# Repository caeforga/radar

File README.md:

# 📡 Software Radar

Sistema de control y visualización para radar meteorológico con interfaz gráfica moderna desarrollada en Python.

## 📋 Descripción

Software Radar es una aplicación de escritorio diseñada para controlar y visualizar datos de un sistema de radar meteorológico en tiempo real. Incluye control de motores, adquisición de datos GPS, integración con sensores meteorológicos y visualización polar de los datos capturados.

### ✨ Características Principales

- 🎮 **Control de Motores**: Control preciso de rotación e inclinación del radar
- 📊 **Visualización en Tiempo Real**: Gráficos polares actualizados en tiempo real
- 🌍 **Integración GPS**: Captura de coordenadas y orientación
- 🌤️ **Datos Meteorológicos**: Monitoreo de temperatura, viento y precipitaciones
- 🔧 **Configuración Avanzada**: Ajuste de ganancia, rango y modos de operación
- 🤖 **Simulación 3D**: Visualización del modelo cinemático del robot
- 💾 **Registro de Datos**: Almacenamiento automático de lecturas

---

## 🚀 Instalación

### Requisitos Previos

- **Python 3.12** o superior
- **Microsoft Visual C++ Build Tools** (necesario para roboticstoolbox)
- **Hardware**: Puerto serial para conexión con el radar

### Paso 1: Instalar Microsoft C++ Build Tools

1. Descarga desde: [Visual C++ Build Tools](https://visualstudio.microsoft.com/visual-cpp-build-tools/)
2. Durante la instalación, selecciona:
   - ✅ **"Desarrollo para el escritorio con C++"**
3. Completa la instalación (puede tardar 10-15 minutos)
4. **Reinicia tu terminal** después de la instalación

### Paso 2: Clonar el Repositorio

```bash
cd C:\Users\TuUsuario\Documents
git clone https://github.com/tuusuario/SoftwareRadar.git
cd SoftwareRadar
```

### Paso 3: Crear Entorno Virtual

```bash
# Crear entorno virtual
python -m venv venv

# Activar entorno virtual
# En Windows PowerShell:
.\venv\Scripts\Activate.ps1

# En Windows CMD:
venv\Scripts\activate.bat

# En Linux/Mac:
source venv/bin/activate
```

### Paso 4: Instalar Dependencias

```bash
# Actualizar pip (recomendado)
python -m pip install --upgrade pip

# Instalar dependencias
pip install -r requirements.txt
```

**⚠️ Nota importante sobre NumPy:**  
El proyecto requiere `numpy<2` debido a incompatibilidades de `roboticstoolbox-python` con NumPy 2.x. Esto ya está especificado en `requirements.txt`.

---

## ▶️ Ejecución

### Ejecutar la Aplicación

```bash
python mejorada.py
```

La interfaz gráfica se abrirá mostrando la pantalla principal con el logo de la facultad y dos botones principales:

- **Control**: Panel de control de motores y conexión serial
- **Visualización**: Panel de visualización del radar

---

## 📖 Guía de Uso

### 1️⃣ Panel de Control

#### Conexión Serial
1. Haz clic en **"Control"**
2. Selecciona el **Puerto COM** correspondiente
3. Selecciona la velocidad (**Baud Rate**, típicamente 9600)
4. Haz clic en **"Conectar"**

#### Modos de Operación
- **OFF**: Radar apagado
- **Standby**: Modo espera (bajo consumo)
- **TEST**: Modo de prueba con controles habilitados
- **ON**: Modo operación completa

#### Control de Motores
- **Motor de Rotación**: Slider horizontal (-180° a +180°)
- **Motor de Inclinación**: Slider vertical (-60° a +60°)
- Los valores se envían al hardware al soltar el slider

#### Configuración del Radar
- **Ganancia**: Ajuste de sensibilidad (-31.5 dB a 0 dB)
- **Inclinación**: Ajuste fino de ángulo (-15° a +15°)
- **Rango**: Botones ▲/▼ para cambiar rango de detección
- **Track (TRK)**: Ajuste del ángulo de seguimiento (◄/►)
- **Perfil Vertical (VP)**: Activar/desactivar modo de escaneo vertical

### 2️⃣ Panel de Visualización

Para acceder a la visualización:
1. Asegúrate de estar **conectado** al puerto serial
2. Haz clic en **"Visualización"**

#### Información Mostrada
- **Gráfico Polar**: Datos del radar en coordenadas polares
- **Estado de Operación**: Indicadores de modo actual
- **Fallos**: Notificaciones de errores del sistema
- **Coordenadas GPS**: Latitud y longitud actuales
- **Orientación**: Dirección de la brújula
- **Datos Meteorológicos**: 
  - Fecha y hora de última lectura
  - Temperatura
  - Dirección del viento
  - Nivel de precipitaciones

#### Interpretación de Colores
- 🟢 **Verde**: Ecos débiles
- 🟡 **Amarillo**: Ecos moderados
- 🔴 **Rojo**: Ecos fuertes
- 🟣 **Magenta**: Ecos muy intensos

---

## 📁 Estructura del Proyecto

```
SoftwareRadar/
├── mejorada.py                 # Aplicación principal
├── ComSerial.py                # Manejo de comunicación serial
├── Interpretacion.py           # Procesamiento de datos del radar
├── GPS.py                      # Procesamiento de datos GPS
├── CargaSensor.py              # Lectura de sensor meteorológico
├── Captura.py                  # Captura de datos con Logic Analyzer
├── ControlMotores.py           # Control de motores
├── GraficoObject.py            # Generación de gráficos
├── requirements.txt            # Dependencias del proyecto
├── README.md                   # Este archivo
│
├── CTkXYFrame/                 # Componente customizado de tkinter
│   ├── __init__.py
│   └── ctk_xyframe.py
│
├── imagenes/                   # Recursos gráficos
│   ├── Icono radar.png
│   ├── Icono palanca.png
│   └── Icono fac.png
│
├── output/                     # Datos capturados
│   ├── Lecturas RADAR/        # Archivos CSV con lecturas
│   └── RawData/                # Datos crudos (.sal)
│
├── FirmwareESP32/              # Firmware para ESP32
│   └── FirmwareESP32.ino
│
└── PCB FINAL/                  # Diseño de PCB (KiCad)
    ├── baquelita.kicad_pcb
    ├── baquelita.kicad_sch
    └── Gerbers/
```

---

## 🔧 Solución de Problemas

### ❌ Error: `ModuleNotFoundError: No module named 'roboticstoolbox'`

**Solución:**
```bash
pip install roboticstoolbox-python
```

### ❌ Error: `numpy.core.multiarray failed to import`

**Causa:** Incompatibilidad entre NumPy 2.x y roboticstoolbox

**Solución:**
```bash
pip uninstall numpy -y
pip install "numpy<2"
```

### ❌ Error: `Microsoft Visual C++ 14.0 or greater is required`

**Solución:**
1. Instala [Visual C++ Build Tools](https://visualstudio.microsoft.com/visual-cpp-build-tools/)
2. Selecciona "Desarrollo para el escritorio con C++"
3. Reinicia la terminal después de la instalación

### ❌ Error: "Sin comunicación serial"

**Solución:**
1. Verifica que el dispositivo esté conectado
2. Comprueba el puerto COM en el Administrador de Dispositivos
3. Asegúrate de tener los drivers correctos instalados
4. Prueba con diferentes velocidades de baudios

### ❌ La aplicación se cierra inmediatamente

**Solución:**
```bash
# Ejecuta desde la terminal para ver mensajes de error
python mejorada.py
```

### ⚠️ Archivo `CR310_RK900_10.csv` no encontrado

**Solución:**
- Asegúrate de que el archivo del sensor meteorológico esté en la carpeta raíz
- Si no tienes el sensor, puedes crear un archivo CSV vacío con las columnas:
  ```csv
  TIMESTAMP,Temperature,Wind_Direction,Precipitation
  ```

---

## 📦 Dependencias

| Paquete | Versión | Descripción |
|---------|---------|-------------|
| customtkinter | 5.2.2 | Interfaz gráfica moderna |
| Pillow | 10.1.0 | Procesamiento de imágenes |
| numpy | <2.0 | Cálculos numéricos |
| matplotlib | 3.8.2 | Generación de gráficos |
| roboticstoolbox-python | 1.1.1 | Cinemática del robot |
| pyserial | 3.5 | Comunicación serial |
| cartopy | 0.25.0 | Mapas geográficos |

---

## 🛠️ Hardware Requerido

- **Radar**: Sistema de radar compatible con protocolo Manchester
- **Motores**: Sistema de 2 grados de libertad (rotación + inclinación)
- **GPS**: Módulo GPS compatible (NMEA)
- **Brújula**: Sensor de orientación
- **Sensor Meteorológico**: Estación meteorológica Campbell Scientific CR310
- **Interfaz**: ESP32 o Arduino para comunicación serial

---

## 📊 Formato de Datos

### Datos de Entrada (Serial)
El sistema espera datos codificados en Manchester con:
- **Tasa de bits**: 1 Mbps
- **Formato**: Tramas de 512 bytes
- **Protocolo**: Custom (ver `Interpretacion.py`)

### Datos GPS
- **Formato**: NMEA (GGA, RMC)
- **Baud Rate**: Configurable

### Sensor Meteorológico
- **Formato**: CSV
- **Columnas**: TIMESTAMP, Temperature, Wind_Direction, Precipitation

---

## 🤝 Contribuir

Las contribuciones son bienvenidas. Por favor:

1. Haz fork del proyecto
2. Crea una rama para tu feature (`git checkout -b feature/AmazingFeature`)
3. Commit tus cambios (`git commit -m 'Add some AmazingFeature'`)
4. Push a la rama (`git push origin feature/AmazingFeature`)
5. Abre un Pull Request

---

## 📄 Licencia

Este proyecto está bajo la Licencia MIT. Ver el archivo `LICENSE` para más detalles.

---

## 👥 Autores

- **Equipo de Desarrollo** - Universidad/Facultad

---

## 📞 Soporte

Si encuentras problemas o tienes preguntas:

1. Revisa la sección de [Solución de Problemas](#-solución-de-problemas)
2. Abre un [Issue](https://github.com/tuusuario/SoftwareRadar/issues) en GitHub
3. Contacta al equipo de desarrollo

---

## 🔄 Changelog

### Versión 1.1.1 (Actual)
- ✅ Soporte para NumPy 1.x
- ✅ Interfaz mejorada con CustomTkinter
- ✅ Visualización de mapas con Cartopy
- ✅ Integración con sensor meteorológico
- ✅ Modo de perfil vertical

---

## ⭐ Agradecimientos

- Robotics Toolbox for Python
- CustomTkinter por la interfaz moderna
- Cartopy por los mapas geográficos
- La comunidad de Python

---

**¡Gracias por usar Software Radar!** 📡✨

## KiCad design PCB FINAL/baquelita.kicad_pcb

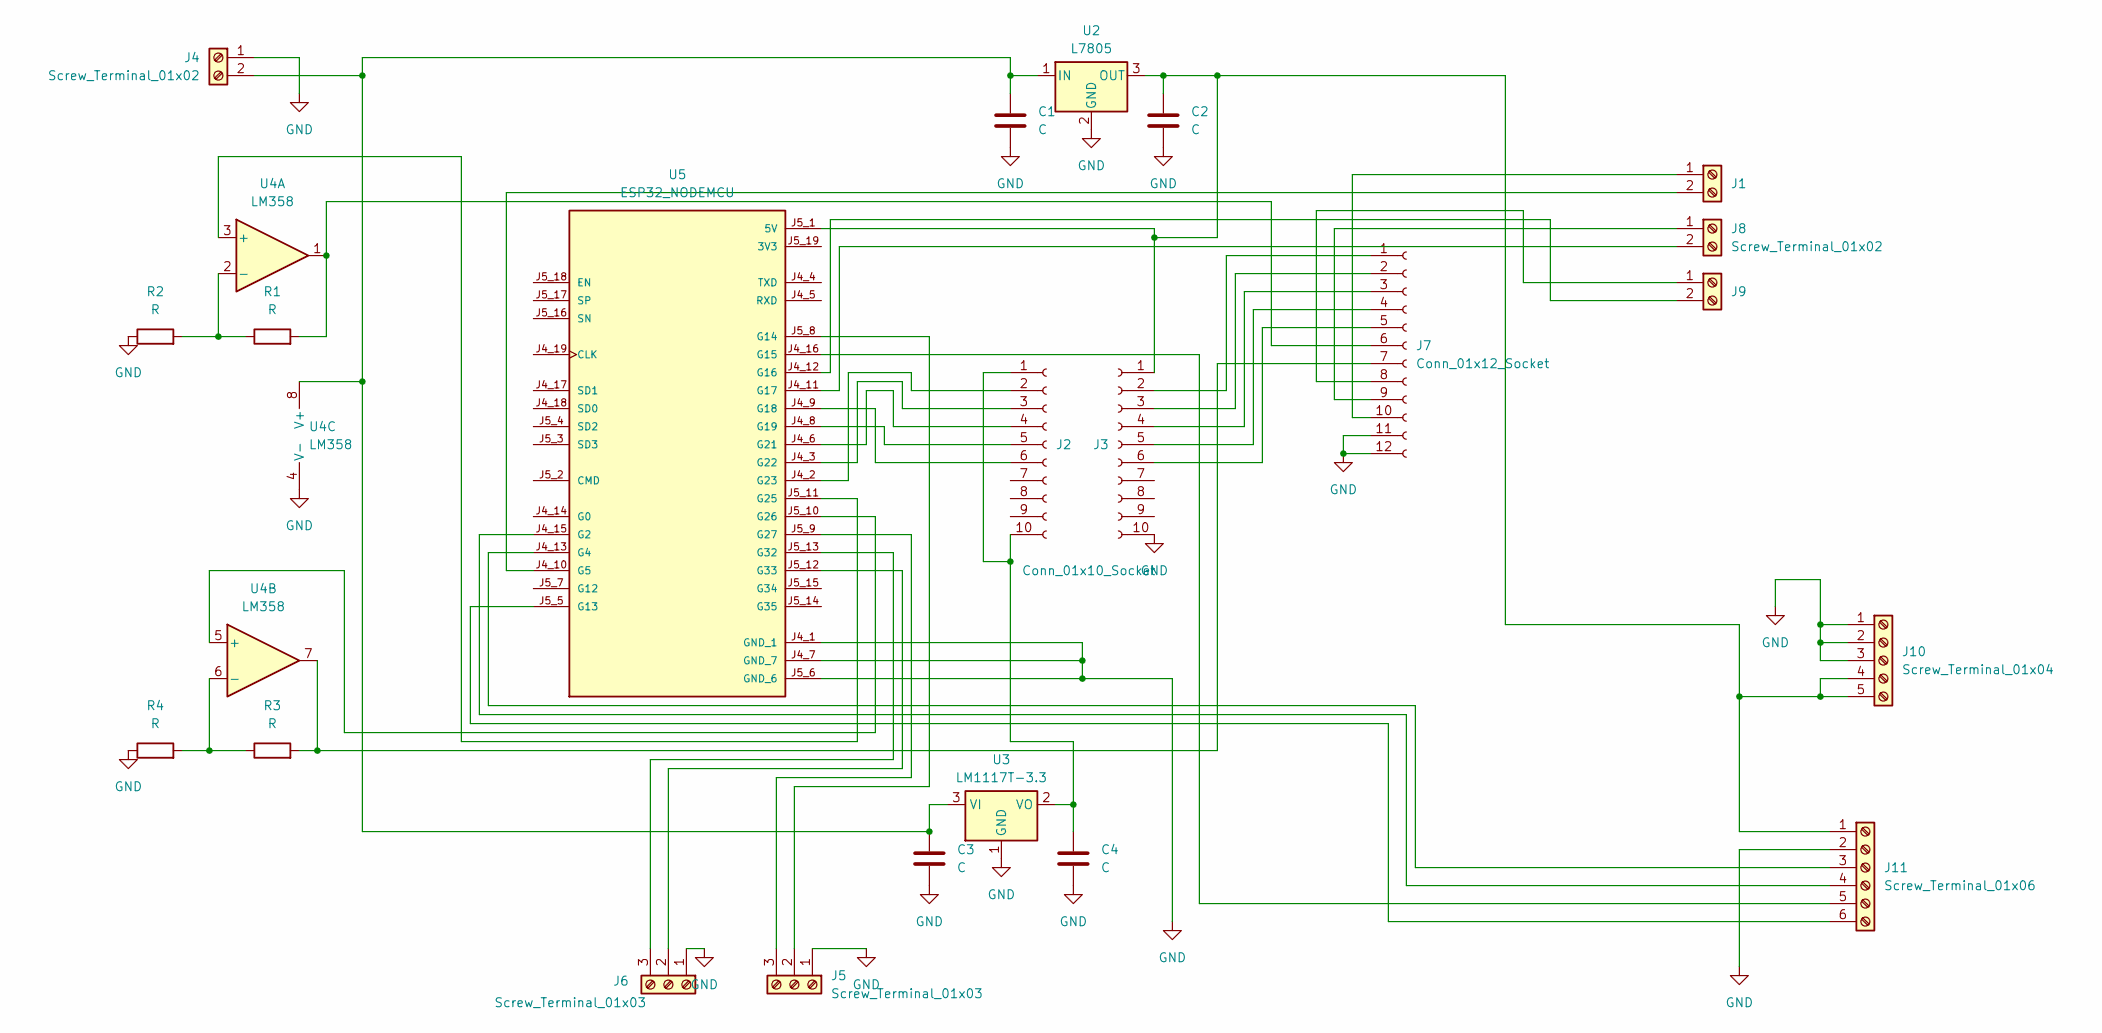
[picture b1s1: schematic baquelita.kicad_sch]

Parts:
C1, C2, C3, C4: C; C_Disc_D7.5mm_W5.0mm_P7.50mm
J1, J4, J8, J9: Screw_Terminal_01x02; TerminalBlock_bornier-2_P5.08mm
J2, J3: Conn_01x10_Socket; PinHeader_1x10_P2.54mm_Vertical
J5, J6: Screw_Terminal_01x03; TerminalBlock_bornier-3_P5.08mm
J7: Conn_01x12_Socket; PinHeader_1x12_P2.54mm_Vertical
J10: Screw_Terminal_01x04; TerminalBlock_bornier-5_P5.08mm
J11: Screw_Terminal_01x06; TerminalBlock_bornier-6_P5.08mm
R1, R2, R3, R4: R; R_Axial_DIN0204_L3.6mm_D1.6mm_P7.62mm_Horizontal
U2: L7805; TO-220-3_Vertical
U3: LM1117T-3.3; TO-220-3_Vertical
U4: LM358; CERDIP-8_W7.62mm_SideBrazed
U5: ESP32_NODEMCU; MODULE_ESP32_NODEMCU

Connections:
GND: C1.2, C2.2, C3.2, C4.2, J3.10, J4.1, J5.1, J6.1, J7.11, J7.12, J10.1, J10.2, J10.3, J11.2, R2.1, R4.1, U2.2 (GND), U3.1 (GND), U4.4 (V-), U5.J4_1 (GND_1), U5.J4_7 (GND_7), U5.J5_6 (GND_6)
unnamed: J1.1, J7.10
unnamed: J1.2, U5.J4_10 (G5)
unnamed: C4.1, J2.1, J2.10, U3.2 (VO)
unnamed: J2.2, U5.J4_2 (G23)
unnamed: J2.3, U5.J4_3 (G22)
unnamed: J2.4, U5.J4_6 (G21)
unnamed: J2.5, U5.J4_8 (G19)
unnamed: J2.6, U5.J4_9 (G18)
unnamed: J3.2, J7.1
unnamed: J3.3, J7.2
unnamed: J3.4, J7.3
unnamed: J3.5, J7.4
unnamed: J3.6, J7.5
unnamed: C1.1, C3.1, J4.2, U2.1 (IN), U3.3 (VI), U4.8 (V+)
unnamed: J5.2, U5.J5_8 (G14)
unnamed: J5.3, U5.J5_9 (G27)
unnamed: J6.2, U5.J5_12 (G33)
unnamed: J6.3, U5.J5_13 (G32)
unnamed: J7.6, R1.2, U4.1
unnamed: J7.7, R3.2, U4.7
unnamed: J7.8, J9.1
unnamed: J7.9, J8.1
unnamed: J8.2, U5.J4_11 (G17)
unnamed: J9.2, U5.J4_12 (G16)
unnamed: C2.1, J3.1, J10.4, J10.5, J11.1, U2.3 (OUT), U5.J5_1 (5V)
unnamed: J11.3, U5.J4_13 (G4)
unnamed: J11.4, U5.J4_15 (G2)
unnamed: J11.5, U5.J4_16 (G15)
unnamed: J11.6, U5.J5_5 (G13)
unnamed: U4.3 (+), U5.J5_11 (G25)
unnamed: R1.1, R2.2, U4.2 (-)
unnamed: U4.5 (+), U5.J5_10 (G26)
unnamed: R3.1, R4.2, U4.6 (-)

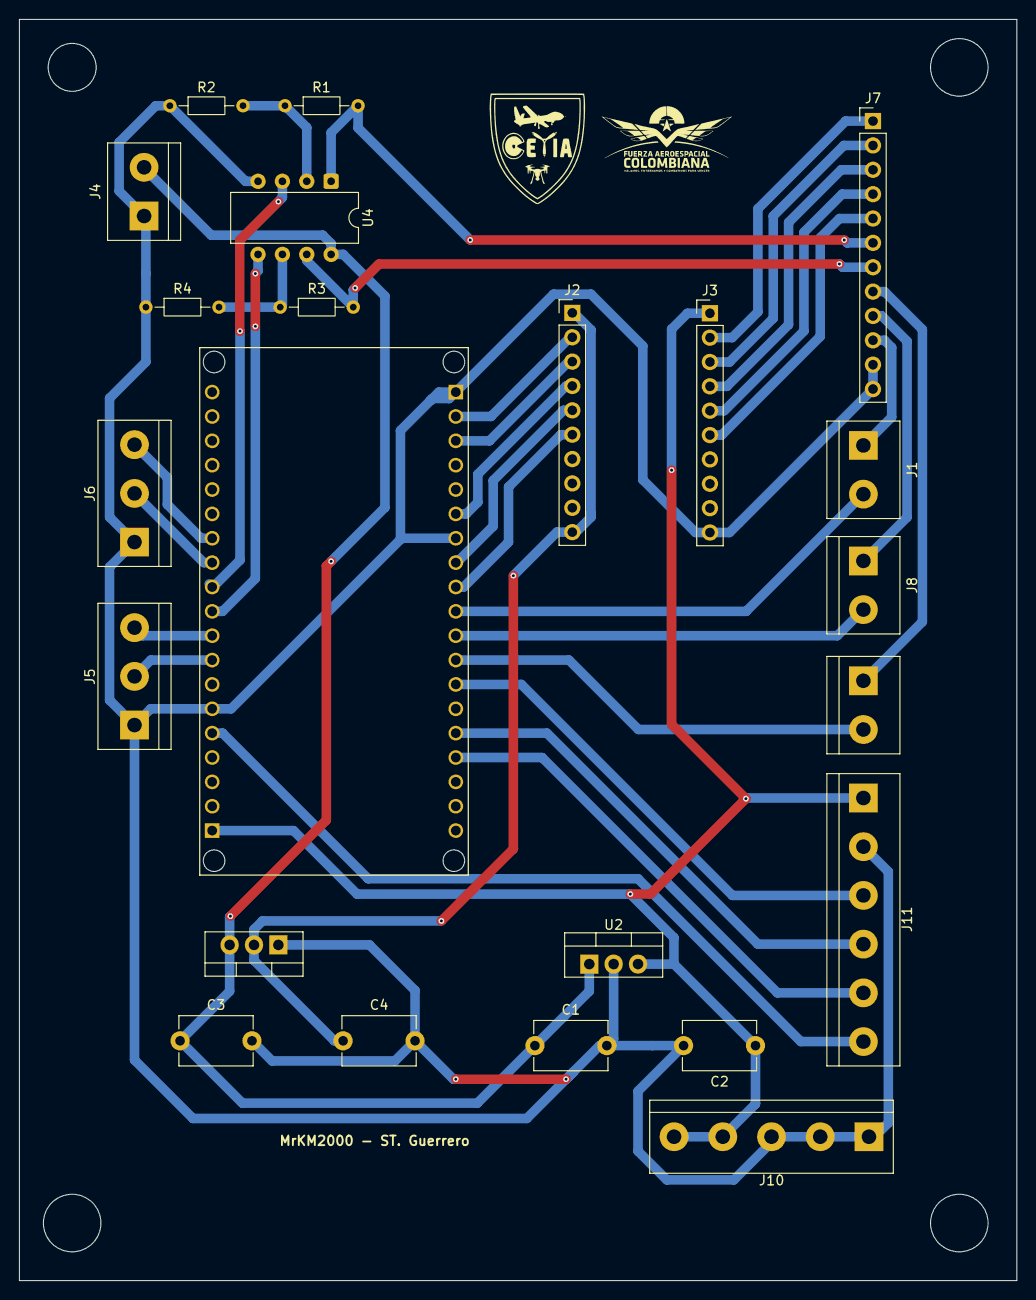
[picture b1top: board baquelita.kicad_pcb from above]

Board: 2 copper layers, 104.0 x 131.5 mm, 23 parts (0 on the bottom side), 34 nets.

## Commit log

2025-11-12 initial commit v1.2
2025-11-12 Add .gitattributes, .gitignore, and GIT_GUIDE.md; include .gitkeep files for output directories
2025-11-14 Complete restructuring of Software Radar to version 2.0, introducing a clean architecture with modular components, centralized configuration, and responsive UI. Added comprehensive documentation, inc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
2025-11-14 Implement responsive design for Control and Visualization panels in Software Radar. Added new responsive panels with dynamic resizing, improved UI layout, and comprehensive documentation. Updated app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
2025-11-17 Add build scripts and documentation for creating standalone executable of Software Radar. Introduced `build_exe.py`, `build.bat`, and `build_simple.bat` for automated compilation. Updated `BUILD_EXEC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
2025-11-17 Optimize button design and icon size in ResponsiveRadarApp for improved UI aesthetics. Adjusted icon dimensions to 35x35 and enhanced button properties for better alignment and visibility. Updated pa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
2025-11-17 Add professional color palette and update button styles in ResponsiveControlPanel for improved UI consistency. Implemented new color scheme reflecting functionality and accessibility principles, enha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
2025-11-18 Implement fix for 3D graph duplication issue in ResponsiveControlPanel. Added logic to destroy the previous Matplotlib canvas before creating a new one, preventing memory leaks and layout issues. Upd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
2025-11-24 Implement fixes for visualization panel issues, addressing duplication and layout problems. Removed redundant grid calls in initialization, added robust widget cleanup before panel transitions, and i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
2025-11-27 Add responsive map panel to Software Radar, integrating interactive map features with radar data overlays. Updated requirements to include `tkintermapview`, modified application structure to support 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
2025-11-29 Add radar icon and enhance map panel functionality in ResponsiveRadarApp. Integrated radar image loading, improved demo mode with simulated data, and refined UI elements for better user experience. U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
2025-12-09 Refactor GPS data reading in ResponsiveVisualizationPanel to include error handling. Added try-except block to manage exceptions during GPS and compass data retrieval, ensuring robust functionality a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
2025-12-26 Enhance radar data handling and UI in Software Radar application. Added error handling for radar data loading in multiple panels, ensuring robust functionality and user feedback. Updated file structu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
2025-12-26 Corrected capture feature and output file.
2025-12-29 Update application title and subtitle in ResponsiveRadarApp to reflect new branding as RADVIS_ART2000, enhancing user recognition and clarity of purpose.
2025-12-29 Add geolocation functionality to ResponsiveVisualizationPanel. Implemented a method to obtain the PC's location using IP-based geolocation services, enhancing the panel's capabilities. Updated initia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
2025-12-29 Revert "Add geolocation functionality to ResponsiveVisualizationPanel. Implemented a method to obtain the PC's location using IP-based geolocation services, enhancing the panel's capabilities. Update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
    This reverts commit a618cca9714d4da4ac5deaf1ea17f7d9522d8c48.
2025-12-29 Add geolocation functionality to ResponsiveMapPanel. Implemented a method to retrieve the PC's location using IP-based geolocation services, enhancing the panel's capabilities. Location is now obtain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
2026-01-02 Update digital sample rate in Captura and enhance import handling in visualization panel. Changed sample rate from 50 MHz to 10 MHz for improved performance. Added optional import for Captura module 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
2026-01-05 Refactor ResponsiveVisualizationPanel for improved layout and compact indicators. Enhanced grid configuration for better responsiveness, updated UI elements for clarity, and added a bottom bar for cr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
2026-01-05 Refactor geolocation handling in ResponsiveMapPanel. Moved location retrieval to occur after widget creation to prevent UI blocking. Implemented thread-safe access to coordinates using a lock, ensuri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
2026-01-28 Enhance 3D radar visualization in ResponsiveControlPanel. Introduced a new method for creating an improved 3D representation of the Bendix King ART 2000 radar, including detailed components such as t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
2026-02-12 Implement geolocation retrieval and enhance UI updates in ResponsiveVisualizationPanel. Added a method to obtain the PC's location using IP-based services, ensuring thread-safe access to coordinates.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
2026-02-20 Refactor 3D radar visualization in ResponsiveControlPanel to improve rendering efficiency. Updated the visualization method to reuse existing figures and canvases, reducing flicker during updates. En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
2026-02-20 Update requirements and enhance Pillow library functionality. Removed numpy version restriction in requirements.txt. Updated Pillow version to 12.1.1, added deprecation warnings for future versions, 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
2026-02-20 update gitignore
2026-02-23 Add Windows Location Service support for geolocation retrieval in map panels
    Enhanced the geolocation functionality in both map_panel_responsive.py and visualization_panel_responsive.py by integrating Windows Location Service for more accurate location data. Implemented fallb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
2026-02-25 Remove obsolete build scripts and compilation guide for Software Radar. The files `BUILD_EXECUTABLE.md`, `build.bat`, and `build_simple.bat` have been deleted to streamline the project structure and 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
2026-02-25 Add comprehensive documentation for project architecture, compilation, and current status
    Introduced several new documents including ARCHITECTURE.md, COMO_COMPILAR.md, COMPILATION_COMPLETE.md, and CURRENT_STATUS.md to provide detailed insights into the project's structure, compilation met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
2026-02-27 Implement loading indicators and deferred loading for control and visualization panels
    Added loading indicators in the ResponsiveRadarApp to enhance user experience during panel transitions. Introduced methods for showing and hiding loading frames, along with animations for visual feed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
2026-03-02 Remove outdated documentation files and streamline project structure
    Deleted several documentation files including ARCHITECTURE.md, COMPILATION_COMPLETE.md, CORRECCION_APLICADA.md, CORRECCION_DUPLICACION_APLICADA.md, CORRECCION_DUPLICACION_PANEL.md, CORRECCION_DUPLICA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
2026-03-04 Refactor 3D box drawing methods in ResponsiveControlPanel for improved clarity and functionality. Removed outdated methods and reintroduced a refined version of the rotated box drawing method, enhanc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

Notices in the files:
README.md:
License: MIT
